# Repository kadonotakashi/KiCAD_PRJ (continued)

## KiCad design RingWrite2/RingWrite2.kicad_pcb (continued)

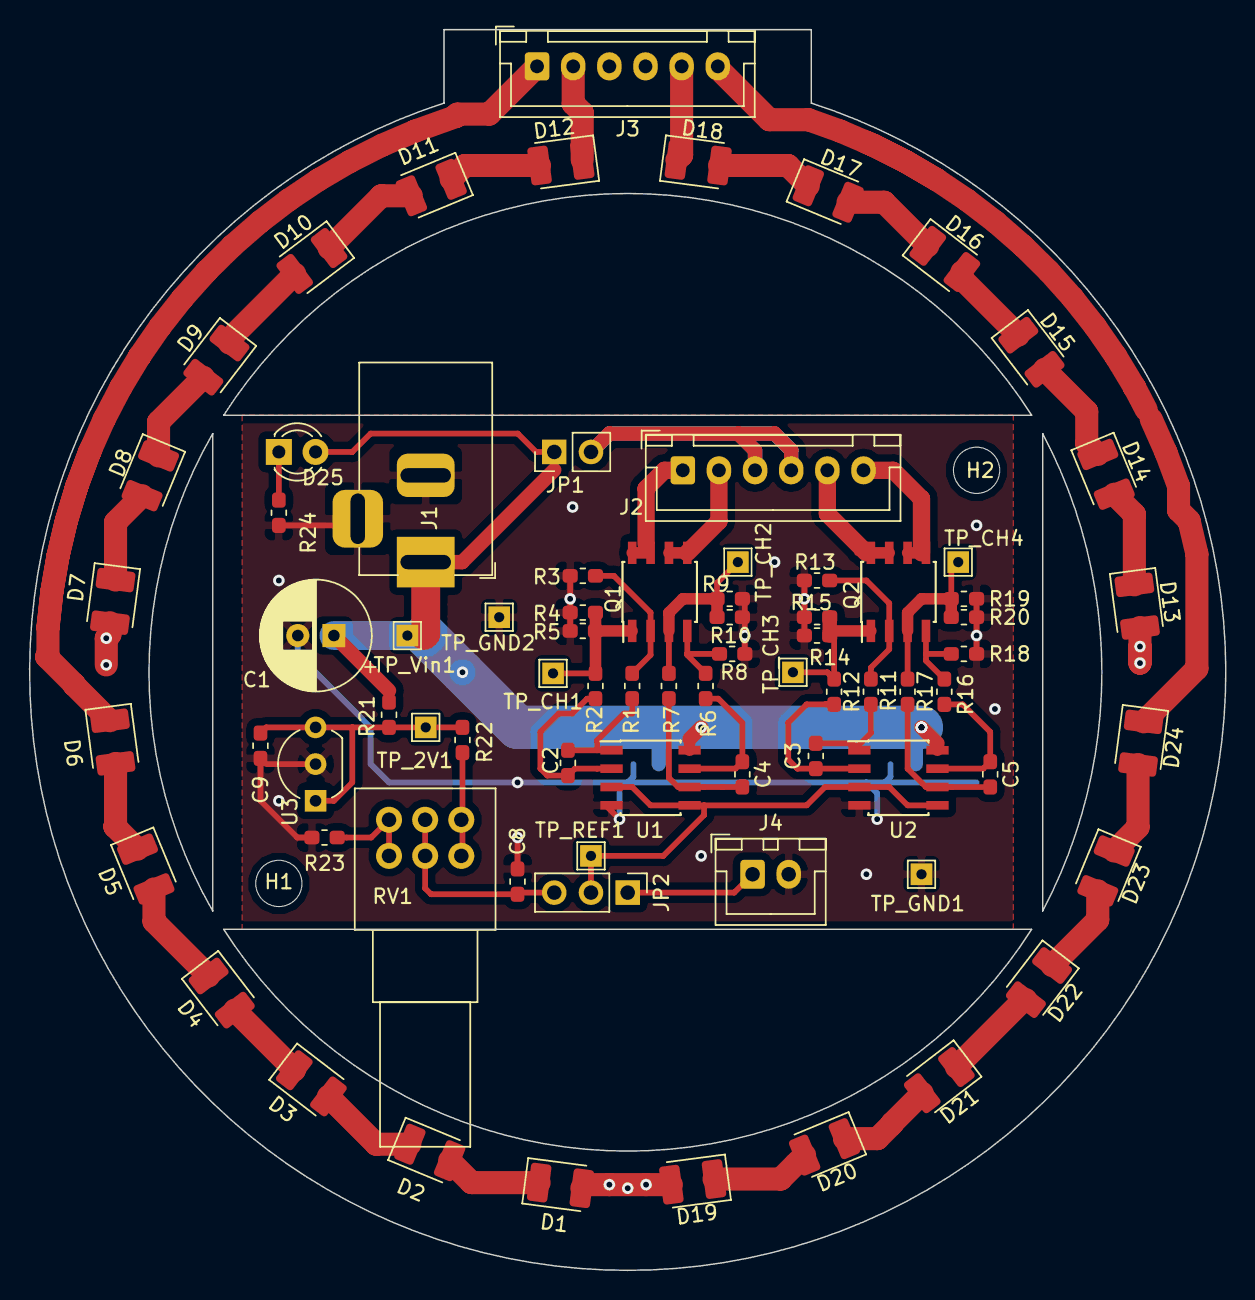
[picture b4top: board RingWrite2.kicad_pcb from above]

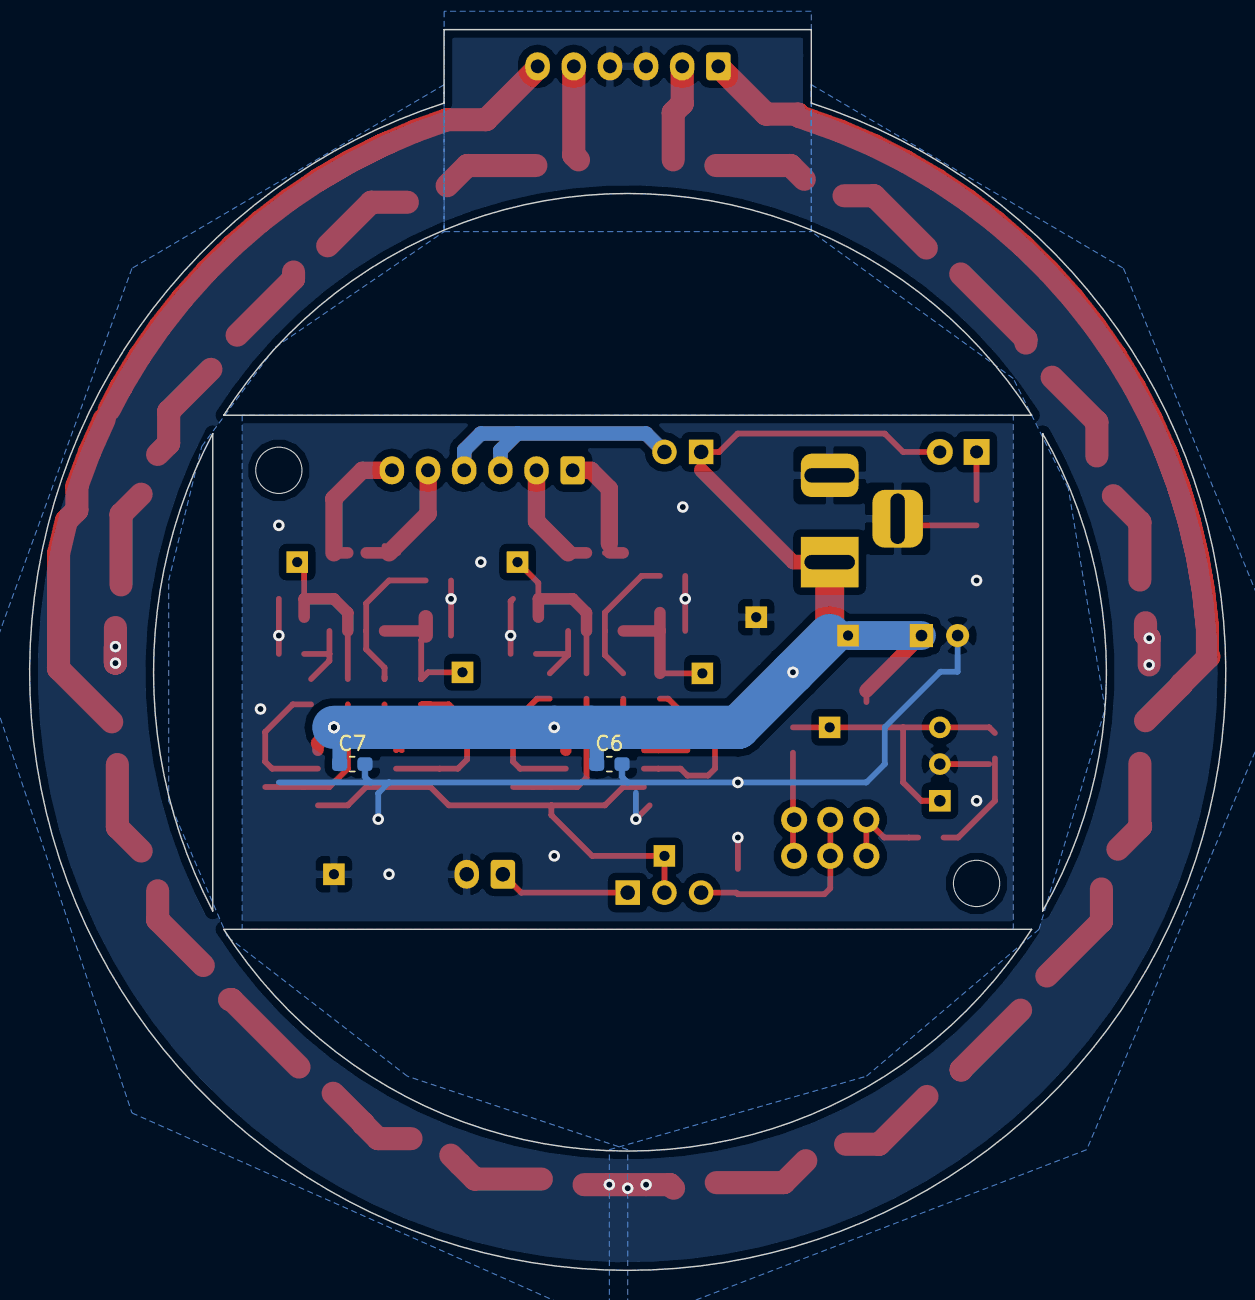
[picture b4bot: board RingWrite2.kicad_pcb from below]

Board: 2 copper layers, 82.7 x 85.8 mm, 81 parts (2 on the bottom side), 55 nets.

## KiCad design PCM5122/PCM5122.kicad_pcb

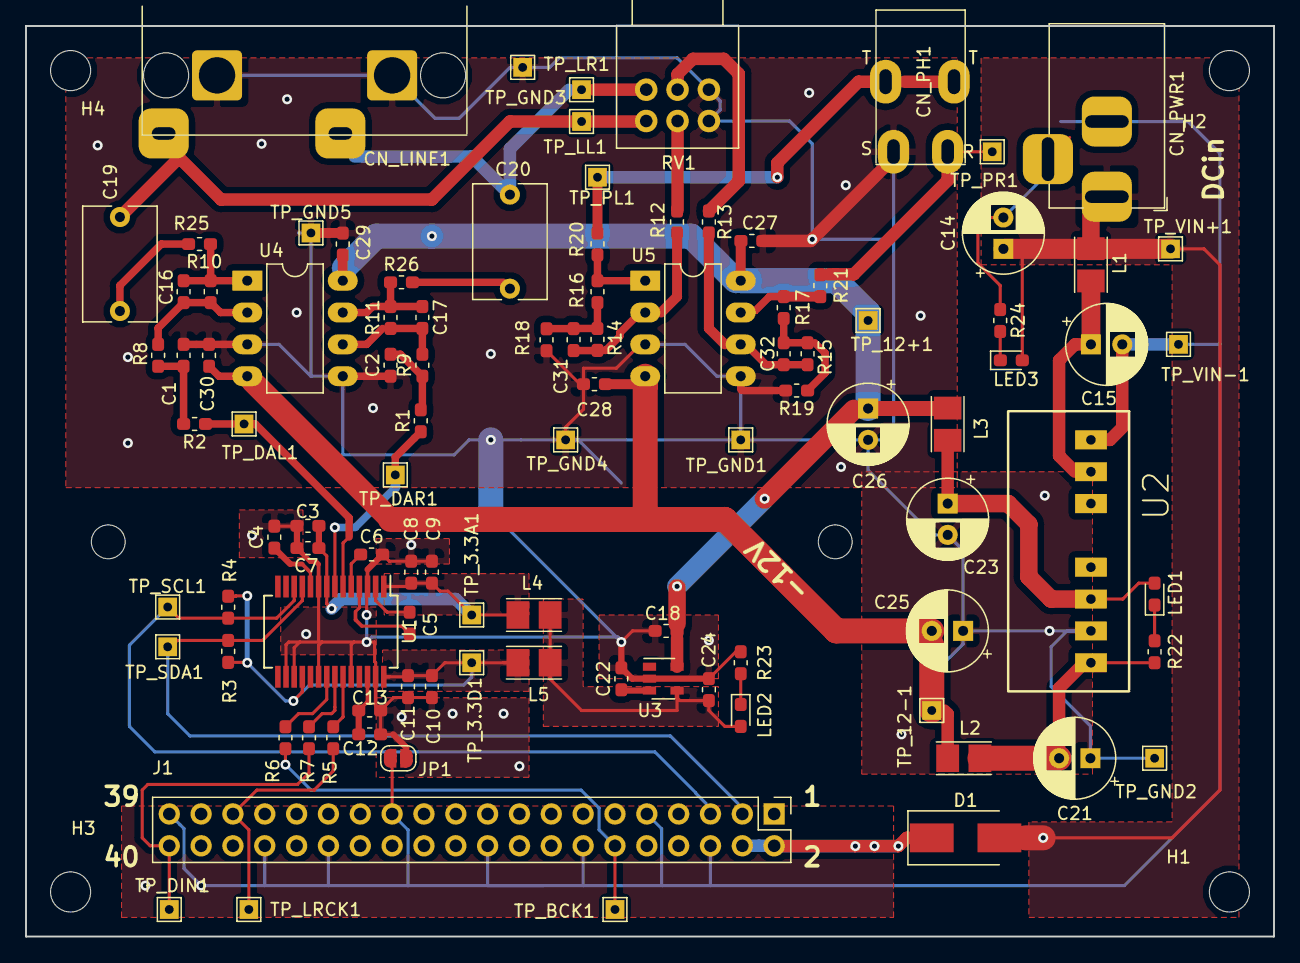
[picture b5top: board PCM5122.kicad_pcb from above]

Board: 2 copper layers, 99.6 x 72.6 mm, 104 parts (0 on the bottom side), 51 nets.

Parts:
C1, C2: 2200p; C_0603_1608Metric_Pad1.05x0.95mm_HandSolder
C3, C4, C8, C10, C12: 10u; C_0603_1608Metric_Pad1.05x0.95mm_HandSolder
C5, C6: 2.2u; C_0603_1608Metric_Pad1.05x0.95mm_HandSolder
C7, C9, C11, C13, C18, C22, C27, C28, C29, C30: 0.1u; C_0603_1608Metric_Pad1.05x0.95mm_HandSolder
C14, C15: 100u/16V; CP_Radial_D6.3mm_P2.50mm
C16, C17: 220p; C_0603_1608Metric_Pad1.05x0.95mm_HandSolder
C19, C20: 2.2u; C_Rect_L9.0mm_W5.7mm_P7.50mm_MKT
C21, C23, C25, C26: 56u/25V; CP_Radial_D6.3mm_P2.50mm
C24: 1u; C_0603_1608Metric_Pad1.05x0.95mm_HandSolder
C31: 5P; C_0603_1608Metric_Pad1.05x0.95mm_HandSolder
C32: 5p; C_0603_1608Metric_Pad1.05x0.95mm_HandSolder
CN_LINE1: Conn_Coaxial_x2; StereoRCA_MJ518
CN_PH1: AudioJack3_Ground; MJ8435_Jack_3.5mm
CN_PWR1: Barrel_Jack_Switch; BarrelJack_Horizontal
D1: RB160M-30TR; D_SMB_Handsoldering
H1, H2, H3, H4: MountingHole; MountingHole_3.2mm_M3
J1: Conn_02x20; RaspberryPi-ZW
JP1: Jumper; SolderJumper-2_P1.3mm_Open_RoundedPad1.0x1.5mm
L1, L2, L3, L4, L5: 10uH; L_Taiyo-Yuden_NR-24xx_HandSoldering
LED1, LED2, LED3: CL-195Y; LED_0603_1608Metric_Pad1.05x0.95mm_HandSolder
R1, R2: 470; R_0603_1608Metric_Pad1.05x0.95mm_HandSolder
R3, R4, R22: 4.7k; R_0603_1608Metric_Pad1.05x0.95mm_HandSolder
R5, R6, R7: 33; R_0603_1608Metric_Pad1.05x0.95mm_HandSolder
R8, R9, R10, R11: 10k; R_0603_1608Metric_Pad1.05x0.95mm_HandSolder
R12, R13, R14, R15: 47k; R_0603_1608Metric_Pad1.05x0.95mm_HandSolder
R16, R17, R24: 1k; R_0603_1608Metric_Pad1.05x0.95mm_HandSolder
R18, R19: 680; R_0603_1608Metric_Pad1.05x0.95mm_HandSolder
R20, R21: 4.7; R_0603_1608Metric_Pad1.05x0.95mm_HandSolder
R23: 330; R_0603_1608Metric_Pad1.05x0.95mm_HandSolder
R25, R26: 100; R_0603_1608Metric_Pad1.05x0.95mm_HandSolder
RV1: R_POT_Dual; Potentiometer_Alps_RK097_Dual_Horizontal
TP_3.3A1, TP_3.3D1, TP_12+1, TP_12-1: TestPoint_THTPad_1.5x1.5mm_Drill0.7mm
TP_BCK1: TestPoint_THTPad_1.5x1.5mm_Drill0.7mm
TP_DAL1: TestPoint_THTPad_1.5x1.5mm_Drill0.7mm
TP_DAR1: TestPoint_THTPad_1.5x1.5mm_Drill0.7mm
TP_DIN1: TestPoint_THTPad_1.5x1.5mm_Drill0.7mm
TP_GND1, TP_GND2, TP_GND3, TP_GND4, TP_GND5: TestPoint_THTPad_1.5x1.5mm_Drill0.7mm
TP_LL1: TestPoint_THTPad_1.5x1.5mm_Drill0.7mm
TP_LR1: TestPoint_THTPad_1.5x1.5mm_Drill0.7mm
TP_LRCK1: TestPoint_THTPad_1.5x1.5mm_Drill0.7mm
TP_PL1: TestPoint_THTPad_1.5x1.5mm_Drill0.7mm
TP_PR1: TestPoint_THTPad_1.5x1.5mm_Drill0.7mm
TP_SCL1: TestPoint_THTPad_1.5x1.5mm_Drill0.7mm
TP_SDA1: TestPoint_THTPad_1.5x1.5mm_Drill0.7mm
TP_VIN+1: TestPoint_THTPad_1.5x1.5mm_Drill0.7mm
TP_VIN-1: TestPoint_THTPad_1.5x1.5mm_Drill0.7mm
U1: PCM5122(I2Cmode); SSOP-28_5.3x10.2mm_P0.65mm
U2: MCW03-05D12; MCW03
U3: NJM2863; SOT-23-5
U4, U5: OPA2134; DIP-8_W7.62mm_LongPads

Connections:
+3.3VA: C3.2, C7.2, C8.2, C9.2, L4.2, TP_3.3A1.1, U1.1, U1.8
+3V3: C10.2, C11.2, L5.2, R3.2, R4.2, TP_3.3D1.1, U1.18, U1.28
+5V: C14.1, CN_PWR1.1, D1.2, L1.1, LED3.2, TP_VIN+1.1
+12VA: C18.1, C26.1, C27.1, C29.1, L3.2, TP_12+1.1, U3.5, U4.8, U5.8
-12VA: C25.2, C28.2, C30.2, L2.2, TP_12-1.1, U4.4, U5.4
/BCK: R6.2, U1.21
/DAoutL: R2.1, TP_DAL1.1, U1.6
/DAoutR: R1.1, TP_DAR1.1, U1.7
/DIN: R7.2, U1.22
/LRCK: R5.1, U1.23
/LoutL: C19.1, CN_LINE1.1, RV1.6, TP_LL1.1
/LoutR: C20.1, CN_LINE1.2, RV1.3, TP_LR1.1
/PoutL: CN_PH1.T, R20.2, TP_PL1.1
/PoutR: CN_PH1.R, R21.2, TP_PR1.1
/SCL: J1.5, R4.1, TP_SCL1.1, U1.12
/SDA: J1.3, R3.1, TP_SDA1.1, U1.11
GNDA: C1.1, C2.1, C3.1, C4.2, C6.2, C7.1, C8.1, C9.1, C10.1, C11.1, C12.2, C13.2, C18.2, C21.1, C22.2, C23.2, C24.2, C25.1, C26.2, C27.2, C28.1, C29.2, C30.1, CN_LINE1.3, CN_PH1.S, JP1.2, R18.2, R19.2, R23.1, RV1.1, RV1.4, TP_GND1.1, TP_GND2.1, TP_GND3.1, TP_GND4.1, TP_GND5.1, U1.3, U1.9, U1.16, U1.17, U1.20, U1.24, U1.27, U2.7, U3.2, U4.3, U4.5, U5.3, U5.5
GNDD: C14.2, C15.2, CN_PWR1.2, CN_PWR1.3, J1.6, J1.9, J1.14, J1.20, J1.25, J1.30, J1.34, J1.39, JP1.1, R24.1, TP_VIN-1.1, U2.1
unnamed: C1.2, R2.2, R8.1
unnamed: C2.2, R1.2, R9.1
unnamed: C4.1, U1.10
unnamed: C5.1, U1.4
unnamed: C5.2, U1.2
unnamed: C6.1, U1.5
unnamed: C12.1, C13.1, U1.26
unnamed: C15.1, L1.2, U2.2
unnamed: C16.1, R10.2, R25.1, U4.1
unnamed: C16.2, R8.2, R10.1, U4.2
unnamed: C17.1, R11.2, R26.1, U4.7
unnamed: C17.2, R9.2, R11.1, U4.6
unnamed: C19.2, R25.2
unnamed: C20.2, R26.2
unnamed: C21.2, L2.1, R22.2, U2.8
unnamed: C22.1, U3.3
unnamed: C23.1, L3.1, LED1.2, U2.6
unnamed: C24.1, L4.1, L5.1, LED2.2, U3.4
unnamed: C31.1, R14.2, R16.2, R18.1
unnamed: C31.2, R12.2, R14.1, U5.2
unnamed: C32.1, R15.2, R17.2, R19.1
unnamed: C32.2, R13.2, R15.1, U5.6
unnamed: D1.1, J1.2, J1.4
unnamed: J1.12, R6.1, TP_BCK1.1
unnamed: J1.35, R5.2, TP_LRCK1.1
unnamed: J1.40, R7.1, TP_DIN1.1
unnamed: LED1.1, R22.1
unnamed: LED2.1, R23.2
unnamed: LED3.1, R24.2
unnamed: R12.1, RV1.5
unnamed: R13.1, RV1.2
unnamed: R16.1, R20.1, U5.1
unnamed: R17.1, R21.1, U5.7

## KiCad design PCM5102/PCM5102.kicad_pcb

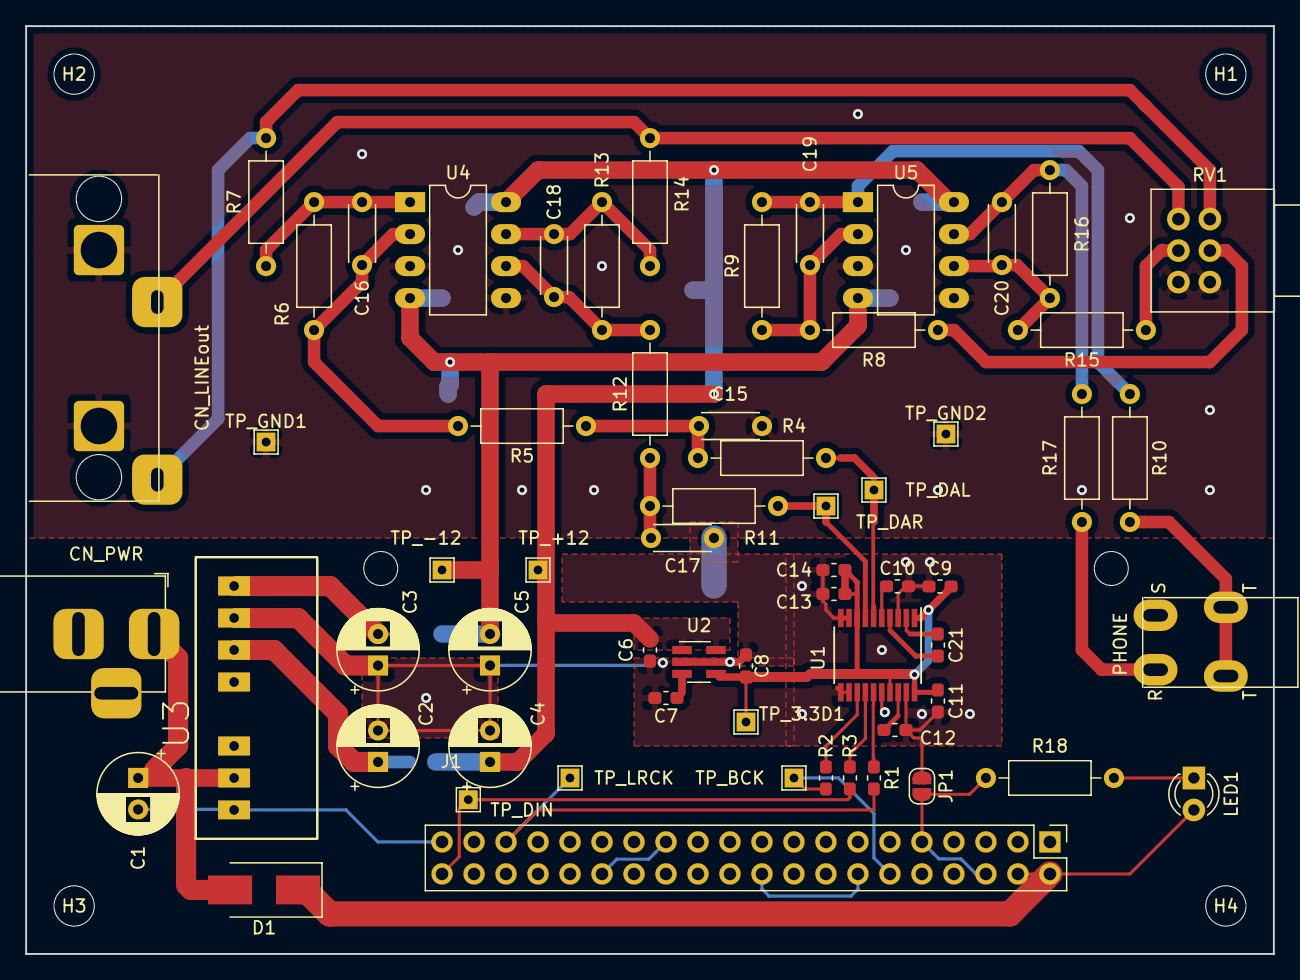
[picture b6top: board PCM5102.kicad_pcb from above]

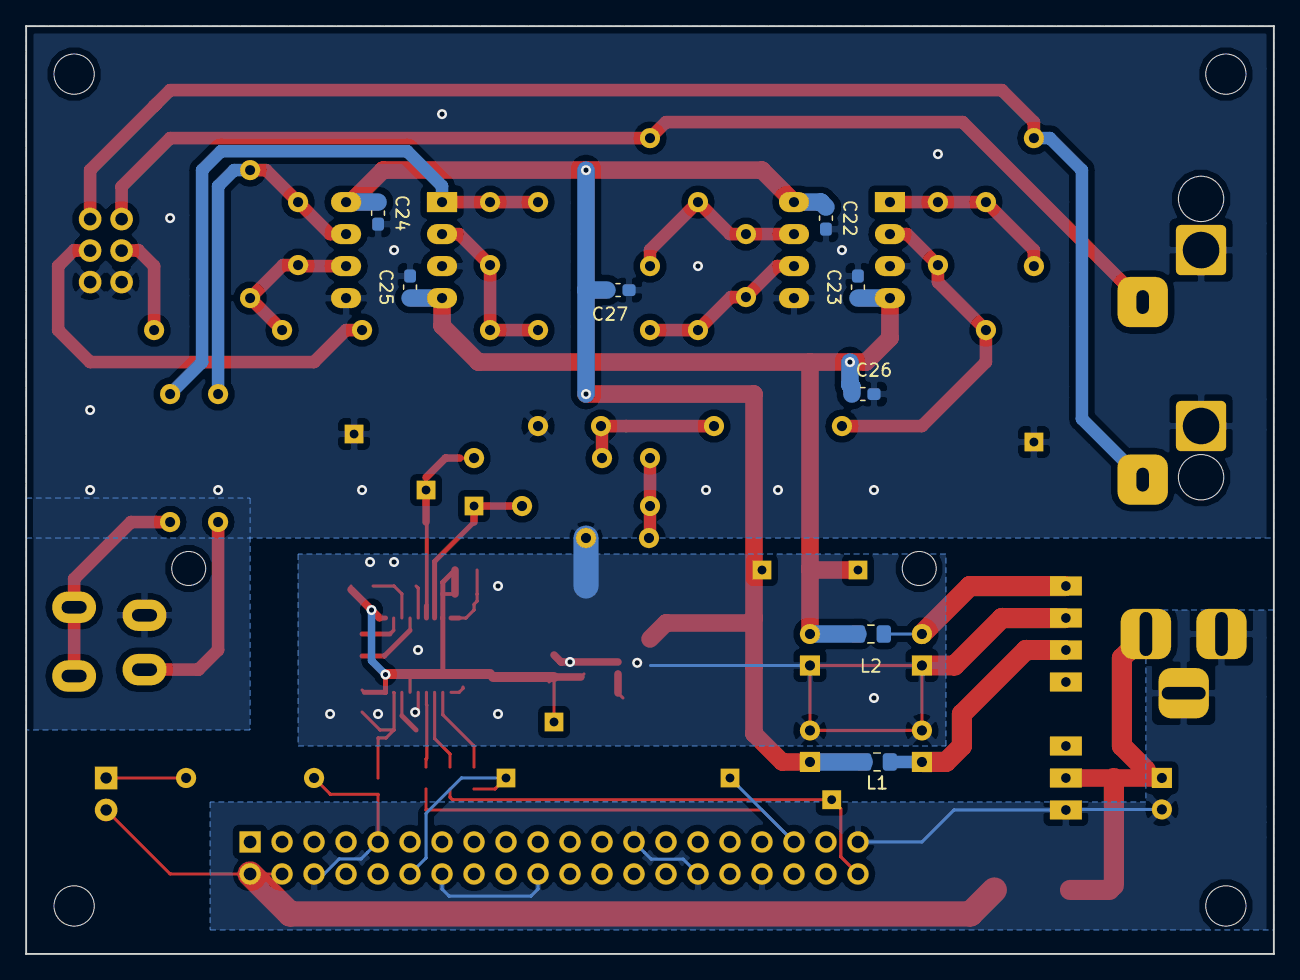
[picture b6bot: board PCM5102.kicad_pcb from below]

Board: 2 copper layers, 99.1 x 73.7 mm, 74 parts (8 on the bottom side), 39 nets.

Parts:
C1: 100u/16V; CP_Radial_D6.3mm_P2.50mm
C2, C3, C4, C5: 56u/25V; CP_Radial_D6.3mm_P2.50mm
C6, C7, C9, C11, C12, C14, C22, C23, C24, C25: 0.1u; C_0603_1608Metric_Pad1.05x0.95mm_HandSolder
C8: 1u; C_0603_1608Metric_Pad1.05x0.95mm_HandSolder
C10, C21: 2.2u; C_0603_1608Metric_Pad1.05x0.95mm_HandSolder
C13, C26, C27: 10u; C_0603_1608Metric_Pad1.05x0.95mm_HandSolder
C15, C17: 2200p; C_Disc_D4.3mm_W1.9mm_P5.00mm
C16, C18: 680p; C_Disc_D4.3mm_W1.9mm_P5.00mm
C19: 5P; C_Disc_D4.3mm_W1.9mm_P5.00mm
C20: 5p; C_Disc_D4.3mm_W1.9mm_P5.00mm
CN_LINEout: Conn_Coaxial_x2; StereoRCA_MJ518
CN_PWR: Barrel_Jack_Switch; BarrelJack_Horizontal
D1: RB160M-30TR; D_SMB_Handsoldering
H1, H2, H3, H4: MountingHole; MountingHole_3.2mm_M3
J1: Conn_02x20; RaspberryPi-ZW
JP1: Jumper; SolderJumper-2_P1.3mm_Open_RoundedPad1.0x1.5mm
L1, L2: LBC2518T100M; L_0805_2012Metric_Pad1.15x1.40mm_HandSolder
LED1: CL-195Y; LED_D3.0mm
PHONE: AudioJack3_Ground; MJ8435_Jack_3.5mm
R1, R2, R3: 33; R_0603_1608Metric_Pad1.05x0.95mm_HandSolder
R4, R11: 470; R_Axial_DIN0207_L6.3mm_D2.5mm_P10.16mm_Horizontal
R5, R6, R12, R13: 4.7k; R_Axial_DIN0207_L6.3mm_D2.5mm_P10.16mm_Horizontal
R7, R14: 100; R_Axial_DIN0207_L6.3mm_D2.5mm_P10.16mm_Horizontal
R8, R9, R15, R16: 47k; R_Axial_DIN0207_L6.3mm_D2.5mm_P10.16mm_Horizontal
R10, R17: 4.7; R_Axial_DIN0207_L6.3mm_D2.5mm_P10.16mm_Horizontal
R18: 1k; R_Axial_DIN0207_L6.3mm_D2.5mm_P10.16mm_Horizontal
RV1: R_POT_Dual; Potentiometer_Alps_RK097_Dual_Horizontal
TP_3.3D1: TestPoint_THTPad_1.5x1.5mm_Drill0.7mm
TP_+12: TestPoint_THTPad_1.5x1.5mm_Drill0.7mm
TP_-12: TestPoint_THTPad_1.5x1.5mm_Drill0.7mm
TP_BCK: TestPoint_THTPad_1.5x1.5mm_Drill0.7mm
TP_DAL: TestPoint_THTPad_1.5x1.5mm_Drill0.7mm
TP_DAR: TestPoint_THTPad_1.5x1.5mm_Drill0.7mm
TP_DIN: TestPoint_THTPad_1.5x1.5mm_Drill0.7mm
TP_GND1, TP_GND2: TestPoint_THTPad_1.5x1.5mm_Drill0.7mm
TP_LRCK: TestPoint_THTPad_1.5x1.5mm_Drill0.7mm
U1: PCM5102; TSSOP-20_4.4x6.5mm_P0.65mm
U2: NJM2863; SOT-23-5_HandSoldering
U3: MCW03-05D12; MCW03
U4, U5: OPA2134; DIP-8_W7.62mm_LongPads

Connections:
+3V3: C8.1, C9.2, C11.1, C13.2, C14.2, TP_3.3D1.1, U1.1, U1.8, U1.17, U1.20, U2.4
+5V: C1.1, CN_PWR.1, D1.2, U3.2
+12VA: C4.1, C6.1, C22.1, C24.1, C27.2, L1.2, TP_+12.1, U2.1, U2.5, U4.8, U5.8
-12VA: C5.2, C23.2, C25.2, C26.1, L2.2, TP_-12.1, U4.4, U5.4
/BCK: R2.2, U1.13
/DAoutL: R4.1, TP_DAL.1, U1.6
/DAoutR: R11.1, TP_DAR.1, U1.7
/DIN: R3.2, U1.14
/LRCK: R1.1, U1.15
/LoutL: CN_LINEout.1, R7.2, RV1.3
/LoutR: CN_LINEout.2, R14.2, RV1.6
/PoutL: PHONE.T, R10.2
/PoutR: PHONE.R, R17.2
GNDA: C2.2, C3.1, C4.2, C5.1, C6.2, C7.2, C8.2, C9.1, C10.2, C11.2, C12.2, C13.1, C14.1, C15.1, C17.1, C22.2, C23.1, C24.2, C25.1, C26.2, C27.1, CN_LINEout.3, JP1.2, PHONE.S, RV1.1, RV1.4, TP_GND1.1, TP_GND2.1, U1.3, U1.9, U1.10, U1.11, U1.12, U1.16, U1.19, U2.2, U3.7, U4.3, U4.5, U5.3, U5.5
GNDD: C1.2, CN_PWR.2, CN_PWR.3, J1.6, J1.9, J1.14, J1.20, J1.25, J1.30, J1.34, J1.39, JP1.1, R18.2, U3.1
unnamed: C2.1, L1.1, U3.6
unnamed: C3.2, L2.1, U3.8
unnamed: C7.1, U2.3
unnamed: C10.1, U1.5
unnamed: C12.1, U1.18
unnamed: C15.2, R4.2, R5.1
unnamed: C16.1, R6.2, R7.1, U4.1
unnamed: C16.2, R5.2, R6.1, U4.2
unnamed: C17.2, R11.2, R12.1
unnamed: C18.1, R13.2, R14.1, U4.7
unnamed: C18.2, R12.2, R13.1, U4.6
unnamed: C19.1, R9.2, R10.1, U5.1
unnamed: C19.2, R8.2, R9.1, U5.2
unnamed: C20.1, R16.2, R17.1, U5.7
unnamed: C20.2, R15.2, R16.1, U5.6
unnamed: C21.1, U1.2
unnamed: C21.2, U1.4
unnamed: D1.1, J1.2, J1.4, LED1.2
unnamed: J1.12, R2.1, TP_BCK.1
unnamed: J1.35, R1.2, TP_LRCK.1
unnamed: J1.40, R3.1, TP_DIN.1
unnamed: LED1.1, R18.1
unnamed: R8.1, RV1.2
unnamed: R15.1, RV1.5

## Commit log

2019-10-22 add PIO Unified Debugger
2019-10-26 add platformio debugger
